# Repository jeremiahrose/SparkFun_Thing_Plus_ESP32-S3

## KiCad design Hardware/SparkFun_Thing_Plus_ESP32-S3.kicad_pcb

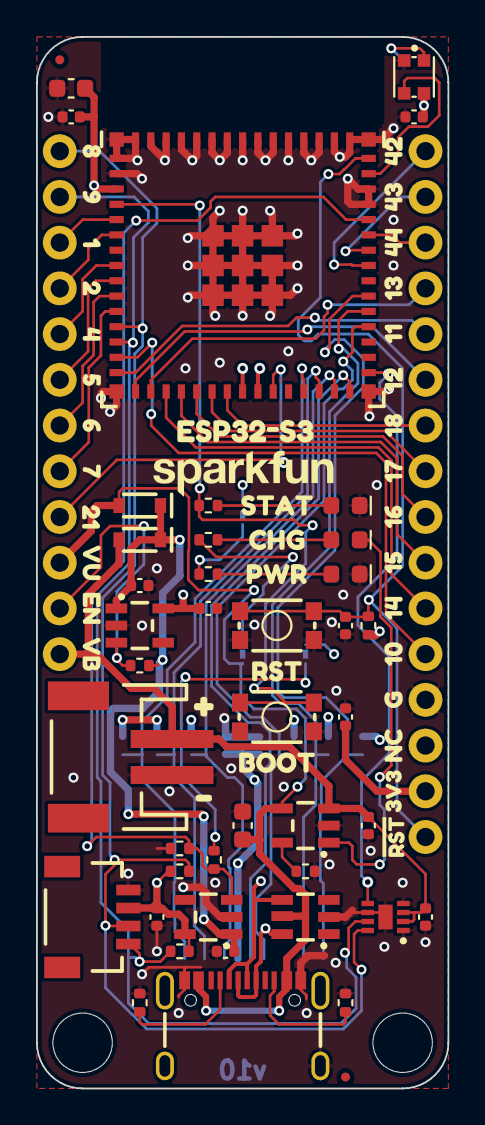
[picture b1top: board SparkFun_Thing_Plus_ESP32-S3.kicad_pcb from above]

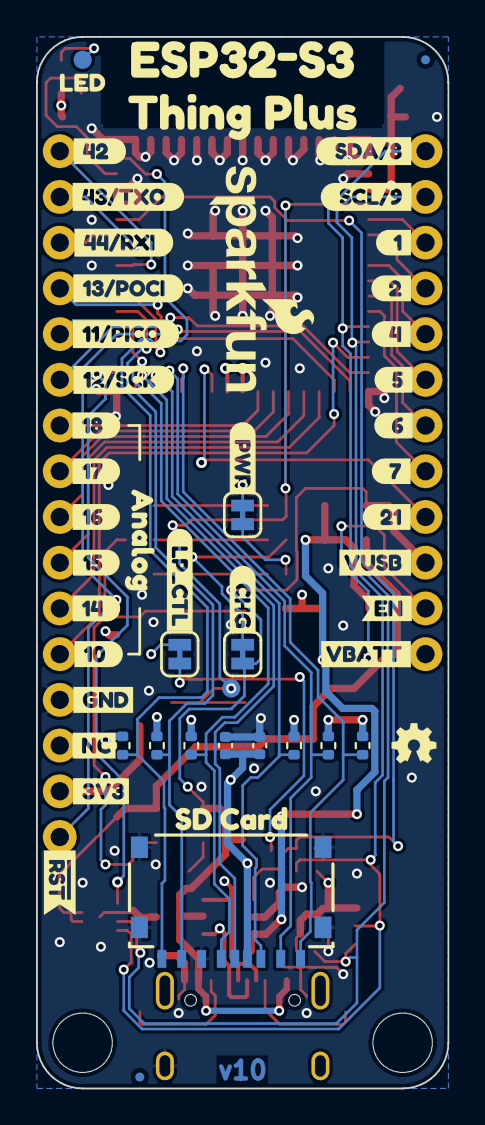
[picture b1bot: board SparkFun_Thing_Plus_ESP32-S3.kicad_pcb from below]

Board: 4 copper layers, 22.9 x 58.4 mm, 137 parts (53 on the bottom side), 53 nets.

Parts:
C1: 22uF; C_0603_1608Metric
C2, C5, C8, C11: 0.1uF; C_0402_1005Metric
C3, C4: 10uF; C_0402_1005Metric
C6, C13: 1.0uF; C_0402_1005Metric
C7, C12: 4.7uF; C_0402_1005Metric
C9: 4.7uF; C_0603_1608Metric
C10, C14: 2.2uF; C_0402_1005Metric
D1: Green; LED_0603_1608Metric
D2, D3: BAT60A; SOD-323
D4: Yellow; LED_0603_1608Metric
D5: Red; LED_0603_1608Metric
D6: WS2812B; WS2812-2020
FID1, FID2, FID3, FID4: Fiducial_0.5mm; Fiducial_0.5mm_Mask1mm
G3: OSHW_Logo; Creative_Commons_License
J1: USB_C_Receptacle; USB-C_16
J2: microSD_Friction; microSD_Friction_Fit_Atom
J3: JST_2mm_LiPo; JST_SMD_2.0mm-2
J4: Qwiic_RA; JST_SMD_1.0mm-4_RA
JP1, JP2, JP3: Jumper_2_NC_Trace
R1, R2, R3, R4, R5, R6, R8, R17: 10k; R_0402_1005Metric
R7: 330; R_0402_1005Metric
R9: 4.7k; R_0402_1005Metric
R10, R11: 5.1k; R_0402_1005Metric
R12, R15: 2.2k; R_0402_1005Metric
R13, R19: 100k; R_0402_1005Metric
R14: 1k; R_0402_1005Metric
R16: 2.0k; R_0402_1005Metric
Ref**: Val**; OSHW_Logo_2.5mm
ST1, ST3: Standoff
SW1, SW2: SMD_4.6x2.8mm_h2.5mm; Momentary_SMD_4.6x2.8mm_h2.5mm
TP1, TP2: 1.0mm; TestPoint-1.0mm
U1, U6: RT9080-3.3; SOT23-5
U2: DT1042-04SO; SOT23-6
U3: ESP32-S3-MINI; ESP32-MINI
U4: MAX17048; DFN-8
U5: MCP73831; SOT23-5
U9: Ordering_Instructions
U10: ThingPlus
kibuzzard-65A99A9C: G***; kibuzzard-65A99A9C
kibuzzard-65A99AA3: G***; kibuzzard-65A99AA3
kibuzzard-65A99E72: G***; kibuzzard-65A99E72
kibuzzard-65A403E0: G***; kibuzzard-65A403E0
kibuzzard-65A992E3: G***; kibuzzard-65A992E3
kibuzzard-65A9923A: G***; kibuzzard-65A9923A
kibuzzard-65A9926C: G***; kibuzzard-65A9926C
kibuzzard-65A9926F: G***; kibuzzard-65A9926F
kibuzzard-65A9927C: G***; kibuzzard-65A9927C
kibuzzard-65A9927F: G***; kibuzzard-65A9927F
kibuzzard-65A9928A: G***; kibuzzard-65A9928A
kibuzzard-65A9928E: G***; kibuzzard-65A9928E
kibuzzard-65A9933C: G***; kibuzzard-65A9933C
kibuzzard-65A9934B: G***; kibuzzard-65A9934B
kibuzzard-65A9935C: G***; kibuzzard-65A9935C
kibuzzard-65A9936B: G***; kibuzzard-65A9936B
kibuzzard-65A9990D: G***; kibuzzard-65A9990D
kibuzzard-65A99252: G***; kibuzzard-65A99252
kibuzzard-65A99268: G***; kibuzzard-65A99268
kibuzzard-65A99274: G***; kibuzzard-65A99274
kibuzzard-65A99278: G***; kibuzzard-65A99278
kibuzzard-65A99283: G***; kibuzzard-65A99283
kibuzzard-65A99287: G***; kibuzzard-65A99287
kibuzzard-65A99292: G***; kibuzzard-65A99292
kibuzzard-65A99297: G***; kibuzzard-65A99297
kibuzzard-65A99335: G***; kibuzzard-65A99335
kibuzzard-65A99346: G***; kibuzzard-65A99346
kibuzzard-65A99350: G***; kibuzzard-65A99350
kibuzzard-65A99354: G***; kibuzzard-65A99354
kibuzzard-65A99359: G***; kibuzzard-65A99359
kibuzzard-65A99360: G***; kibuzzard-65A99360
kibuzzard-65A99364: G***; kibuzzard-65A99364
kibuzzard-65A99367: G***; kibuzzard-65A99367
kibuzzard-65A99912: G***; kibuzzard-65A99912
kibuzzard-65A99933: G***; kibuzzard-65A99933
kibuzzard-65AA9C9F: G***; kibuzzard-65AA9C9F
kibuzzard-656A3D93: G***; kibuzzard-656A3D93
kibuzzard-656A31AF: G***; kibuzzard-656A31AF
kibuzzard-656A32A0: G***; kibuzzard-656A32A0
kibuzzard-656A32FE: G***; kibuzzard-656A32FE
kibuzzard-656A35A5: G***; kibuzzard-656A35A5
kibuzzard-656A35AD: G***; kibuzzard-656A35AD
kibuzzard-656A35B5: G***; kibuzzard-656A35B5
kibuzzard-656A35BC: G***; kibuzzard-656A35BC
kibuzzard-656A35C4: G***; kibuzzard-656A35C4
kibuzzard-656A36A2: G***; kibuzzard-656A36A2
kibuzzard-656A36A7: G***; kibuzzard-656A36A7
kibuzzard-656A36C2: G***; kibuzzard-656A36C2
kibuzzard-656A47C5: G***; kibuzzard-656A47C5
kibuzzard-656A359E: G***; kibuzzard-656A359E
kibuzzard-656A361F: G***; kibuzzard-656A361F
kibuzzard-656A367B: G***; kibuzzard-656A367B
kibuzzard-656A368C: G***; kibuzzard-656A368C
kibuzzard-656A482A: G***; kibuzzard-656A482A
kibuzzard-656A3526: G***; kibuzzard-656A3526
kibuzzard-656A3552: G***; kibuzzard-656A3552
kibuzzard-656A3559: G***; kibuzzard-656A3559
kibuzzard-656A3560: G***; kibuzzard-656A3560
kibuzzard-656A3567: G***; kibuzzard-656A3567
kibuzzard-656A3591: G***; kibuzzard-656A3591
kibuzzard-656A3598: G***; kibuzzard-656A3598
kibuzzard-656A3668: G***; kibuzzard-656A3668
kibuzzard-656A3687: G***; kibuzzard-656A3687
kibuzzard-656A3691: G***; kibuzzard-656A3691
kibuzzard-656A3878: G***; kibuzzard-656A3878
kibuzzard-656A4896: G***; kibuzzard-656A4896
kibuzzard-6569BE4A: G***; kibuzzard-6569BE4A
kibuzzard-6569BE28: G***; kibuzzard-6569BE28
kibuzzard-6569BE57: G***; kibuzzard-6569BE57
kibuzzard-6569BF02: G***; kibuzzard-6569BF02
kibuzzard-6569F7FC: G***; kibuzzard-6569F7FC
kibuzzard-6569F8A4: G***; kibuzzard-6569F8A4

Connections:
3.3V: C1.2, C7.1, C11.1, C13.1, JP1.2 (B), JP2.2 (B), R8.1, U3.3 (3V3), U6.5 (VOUT), U10.27 (3.3V)
3.3V_P: C3.1, C4.1, C5.1, C8.1, D6.4 (VDD), J2.4 (VDD), J4.2, R1.1, R2.1, R3.1, R4.1, R5.1, R6.1, R12.1, R15.1, U1.5 (VOUT)
EN: R13.2, U6.3 (EN), U10.11 (EN)
ESP0/STAT: R7.1, SW1.1 (A), TP2.1, U3.4 (IO0)
ESP1: U3.5 (IOA1), U10.3 (GPIO6)
ESP2: U3.6 (IOA2), U10.4 (GPIO5)
ESP4: U3.8 (IOA4), U10.5 (GPIO4)
ESP5: U3.9 (IOA5), U10.6 (GPIO3)
ESP6: U3.10 (IOA6), U10.7 (GPIO2)
ESP7: U3.11 (IOA7), U10.8 (GPIO1)
ESP8/SDA: J4.3, R15.2, U3.12 (IOA8), U4.8 (SDA), U10.1 (SDA)
ESP9/SCL: J4.4, R12.2, U3.13 (IOA9), U4.7 (SCL), U10.2 (SCL)
ESP10/A0: U3.14 (IOA10), U10.24 (A0)
ESP11/PICO: U3.15 (IOA11), U10.17 (PICO)
ESP12/SCK: U3.16 (IOA12), U10.18 (SCK)
ESP13/POCI: U3.17 (IOA13), U10.16 (POCI)
ESP14/A1: U3.18 (IOA14), U10.23 (A1)
ESP15/A2: U3.19 (IOA15), U10.22 (A2)
ESP16/A3: U3.20 (IOA16), U10.21 (A3)
ESP17/A4: U3.21 (IOA17), U10.20 (A4)
ESP18/A5: U3.22 (IOA18), U10.19 (A5)
ESP19/D-: J1.A7 (D-), J1.B7 (D-), U2.4 (I/O3), U3.23 (IOA19)
ESP20/D+: J1.A6 (D+), J1.B6 (D+), U2.6 (I/O4), U3.24 (IOA20)
ESP21: U3.25 (IO21), U10.9 (GPIO0)
ESP33/SDIO3: J2.2 (DAT3/~CS), R6.2, U3.28 (IO33)
ESP34/SDIO_CMD: J2.3 (CMD/SDI), R1.2, U3.29 (IO34)
ESP35/~ALRT: U3.31 (IO35), U4.5 (~ALRT)
ESP38/SDIO_CLK: J2.5 (CLK/SCK), R2.2, U3.34 (IO38)
ESP39/SDIO0: J2.7 (DAT0/SDO), R3.2, U3.35 (IO39)
ESP40/SDIO1: J2.8 (DAT1), R4.2, U3.36 (IO40)
ESP42/FREE: U3.38 (IO42), U10.13 (FREEBIE)
ESP43/TXO: U3.39 (TXD0/IO43), U10.14 (TX)
ESP44/RXI: U3.40 (RXD0/IO44), U10.15 (RX)
ESP45/Q_EN: R17.2, R19.1, U1.3 (EN), U3.41 (IO45)
ESP46/LED: D6.3 (DIN), U3.44 (IO46)
ESP47/SDIO2: J2.1 (DAT2), R5.2, U3.27 (IO47)
ESP48/SDIO_~DET: J2.9 (DET), U3.30 (IO48)
ESP~RST: C6.1, R8.2, SW2.1 (A), U3.45 (EN), U10.28 (~RESET)
GND: C1.1, C2.2, C3.2, C4.2, C5.2, C6.2, C7.2, C8.2, C9.2, C10.2, C11.2, C12.2, C13.2, C14.2, D1.1 (K), D5.1 (K), D6.2 (VSS), J1.GND, J1.S (SHIELD), J2.6 (VSS), J2.10 (SHIELD), J3.1 (-), J4.1, R10.1, R11.2, R16.2, R19.2, SW1.2 (B), SW2.2 (B), U1.2 (GND), U2.2 (GND), U3.1 (GND), U3.2 (GND), U3.42 (GND), U3.43 (GND), U3.46 (GND), U3.47 (GND), U3.48 (GND), U3.49 (GND), U3.50 (GND), U3.51 (GND), U3.52 (GND), U3.53 (GND), U3.54 (GND), U3.55 (GND), U3.56 (GND), U3.57 (GND), U3.58 (GND), U3.59 (GND), U3.60 (GND), U3.61 (GND), U3.62 (GND), U3.63 (GND), U3.64 (GND), U3.65 (GND), U4.1 (CTG), U4.4 (GND), U4.6 (QSTRT), U4.9 (GND), U5.2 (GND), U6.2 (GND), U10.25 (GND)
unnamed: D1.2 (A), R7.2
unnamed: D4.2 (A), R14.1
unnamed: D4.1 (K), U5.1 (STAT)
unnamed: D5.2 (A), R9.2
unnamed: D6.1 (DOUT), TP1.1
unnamed: J1.A5 (CC1), R11.1
unnamed: J1.B5 (CC2), R10.2
unnamed: JP1.1 (A), R9.1
unnamed: JP2.1 (A), R17.1
unnamed: JP3.1 (A), R14.2
unnamed: R16.1, U5.5 (PROG)
VBATT: C2.1, C12.1, D3.A, J3.2 (+), U4.2 (CELL), U4.3 (VDD), U5.3 (V_{BAT}), U10.12 (V_BATT)
VIN: C10.1, C14.1, D2.C, D3.C, R13.1, U1.1 (VIN), U6.1 (VIN)
VUSB: C9.1, D2.A, J1.VBUS, JP3.2 (B), U2.5 (VCC), U5.4 (VIN), U10.10 (V_USB)

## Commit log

2024-01-15 Remove single unit production files
2024-01-15 Update rev number
2024-01-15 Update test sketches
2024-01-18 Updates post review
2024-01-19 Add default on to Qwiic power.
2024-02-06 Initial Docs Commit
    Adding GH pages build/background files & initial documentation content commit.
2024-02-15 Revise layout post design review
2024-02-16 Docs Update
    Initial commit for software setup & examples sections. Minor edits to Hardware Overview.
2024-02-16 Fix 330 prod ID. Update parts to new naming conventions
2024-02-21 Update comments on example sketches
2024-02-23 Docs update
    Updating Arduino examples w/more detail & info on esptool upload errors.
2024-02-27 Docs Update
    Adding board files/assets and updating relevant sections. Prepping examples section for release.
2024-02-29 Docs Photos update
    Adding photo assets and inline links to them.
2024-03-12 Update README.md
    Updating README.md with updated product info/photos/etc.
2024-03-20 Docs build update
    Adding page build files & final review edits. Removing code snippets for examples to fix build errors but will re-add them once the repo is public.
2024-03-28 Go Live Updates
    Adding code snippets, stylesheet & contribute/file issue files.
2024-03-28 Update software_setup
    Cleanup of pre-release notes.
2024-10-25 Update mkdocs.yml
    Analytics update
2024-11-15 Update with current models and symbols
2024-11-15 Deployed c9fc69f with MkDocs version: 1.6.1
2024-12-22 Add PlatformIO instructions
2024-12-22 Board definition has now been merged to `pioarduino/platform-espressif32`

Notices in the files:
parts and their libraries:
Released under the Creative Commons Attribution Share-Alike 4.0 License
https://creativecommons.org/licenses/by-sa/4.0
